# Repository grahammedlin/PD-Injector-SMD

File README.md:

**!!! Use at your own risk. 
May kill USB ports or worse. !!!**

Definitely don't connect two USB-C-to-A cables between your two favorite computers.

# PD-Injector 

Based on earlier versions by [Jana-Marie Hemsing](https://github.com/Jana-Marie/PD-Injector), [Clara Hobbs](https://git.clarahobbs.com/pd-buddy/pd-buddy-wye), and [tinyledmatrix](https://github.com/tinyledmatrix/PD-Injector-SMD).

This is a USB power delivery Power/Data injector. This version uses all USB-C receptacles. The data lines from one input and the power lines from the other are combined and present at the output. Therefore you can have a data connection from your (not PD capable) computer, while having power from a power supply. It only connects the USB2.0 data lines. Two receptacles means you will need to orient the power cables in the same direction.

Why? Earlier versions appear for Android Auto, where the head unit was insufficient to charge while running. The [Coolgear PD Injector](https://www.coolgear.com/product/usb-c-usb-b-power-delivery-adapter-wmounting-kit) is expensive. I'm using this to program devices while powered, e.g. the [PINECIL V2 soldering iron](https://wiki.pine64.org/wiki/Pinecil_Power_Supplies) and that [MHP30 tiny hotplate](https://www.adafruit.com/product/4948), and potentially run a 3D printer toolhead over USB instead of CAN+Power. These [HUSB328-based USB-C trigger boards](https://www.amazon.com/Coolgear-Delivery-Injector-Type-C-Device/dp/B075F6BD4Y/) are helpful for debugging. 

Interestingly, the Pinecil and MHP30 both use the Onsemi FUSB302MPX, but the Pinecil will not power if the second cable is an active cable like Thunderbolt, while the MHP30 will just fine.

90 W power supply to read a USB-A thumb drive? Sure.

[//]: # (Connecting two devices with USB Type C receptacles with a USB Type C cable is the intended use. But if one receptacle isn't a device but a passive board, that's a problem.)
[//]: # (An E-Marker is required on all USB Type-C cables that support 5 amps and/or exceed 60 watts of power carrying capability)

# License
CERN Open Hardware Licence v1.2.  See LICENSE for more information.

## References
- [USB.org PD](https://www.usb.org/sites/default/files/D2T2-1%20-%20USB%20Power%20Delivery.pdf)
- [USB.org card edge gerbers](https://www.usb.org/document-library/usb-type-c-cable-assembly-signal-integrity-test-fixture-gerber-files)

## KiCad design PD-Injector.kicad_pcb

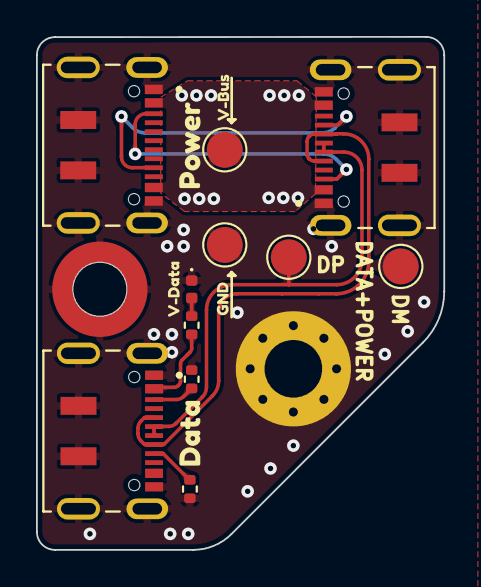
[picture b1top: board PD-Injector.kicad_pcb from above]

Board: 2 copper layers, 22.6 x 28.5 mm, 18 parts (0 on the bottom side), 10 nets.

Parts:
D1: LED; LED_0402_1005Metric
H2: M2x0.5mm SMD Spaccer; WA-SMSI_9774005243
MK1: M3; MountingHole_3.2mm_M3_Pad_Via
R1, R2, R3: 5.1k; R_0402_1005Metric
TP1, TP2, TP2#2, TP2#3: TestPoint; TestPoint_Pad_D2.0mm
USB-C1, USB-C2, USB-C3: USB_C_Receptacle_USB2.0; JAE_DX07S016JA1R1500
kibuzzard-6334B7AE: G***; kibuzzard-6334B7AE
kibuzzard-6334B838: G***; kibuzzard-6334B838
kibuzzard-6334B904: G***; kibuzzard-6334B904
kibuzzard-63322175: G***; kibuzzard-63322175
kibuzzard-63322190: G***; kibuzzard-63322190

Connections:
/CC1D: R1.1, USB-C2.A5 (CC1)
/CC1P: USB-C1.A5 (CC1), USB-C3.A5 (CC1)
/CC2D: R2.2, USB-C2.B5 (CC2)
/CC2P: USB-C1.B5 (CC2), USB-C3.B5 (CC2)
/D+: TP2#3.1, USB-C2.A6 (D+), USB-C2.B6 (D+), USB-C3.A6 (D+), USB-C3.B6 (D+)
/D-: TP2#2.1, USB-C2.A7 (D-), USB-C2.B7 (D-), USB-C3.A7 (D-), USB-C3.B7 (D-)
GND: D1.1 (K), H2.1, MK1.1, R1.2, R2.1, TP2.1, USB-C1.A1 (GND), USB-C1.S1 (SHIELD), USB-C2.A1 (GND), USB-C2.S1 (SHIELD), USB-C3.A1 (GND), USB-C3.S1 (SHIELD)
unnamed: D1.2 (A), R3.2
unnamed: R3.1, USB-C2.A4 (VBUS)
VBUS: TP1.1, USB-C1.A4 (VBUS), USB-C3.A4 (VBUS)

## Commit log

2022-09-27 Initial cleanup and first push of edited Kicad/Readme
2022-09-29 change of form factor and further ECAD work
2022-10-12 finalized PCB work for V0.1
2022-10-13 minor schematic clean up
2022-10-14 minor changes
2022-11-14 minor chnages
2023-02-24 updated kicad 7
2023-02-25 Swapped output to receptacle
2023-02-27 Update readme, minor mucking about
2023-02-28 update pdf, cleanup
2023-03-02 switch USB-C part
2023-03-02 bom update
2023-03-04 more vbus copper
2023-03-13 update readme with photo
2023-03-14 add photo to Readme
2023-03-15 add enclosure
2023-03-16 add USB2.0 test pads
